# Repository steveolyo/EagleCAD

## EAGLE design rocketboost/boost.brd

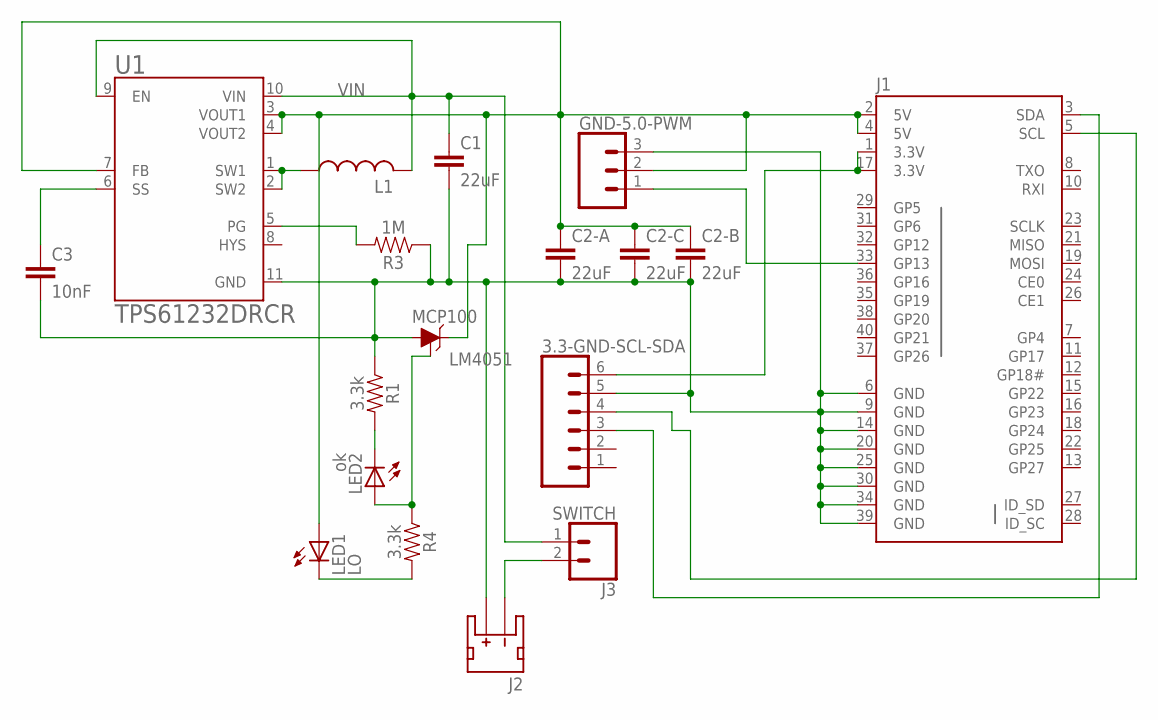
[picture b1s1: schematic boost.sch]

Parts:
3.3-GND-SCL-SDA: CONN_06POLAR; MOLEX-1X6
C1, C2-A, C2-B, C2-C: 22uF; C0603
C3: 10nF; C0603
GND-5.0-PWM: CONN_03; 1X03
J1: RASPBERRYPI-40-PIN-GPIO_PTH_NO_SHROUD; 2X20
J2: PWR; JST-2-SMD
J3: SWITCH; 1X02
L1: L-USL4532C; L4532M
LED1: LO; CHIP-LED0603
LED2: ok; CHIP-LED0603
MCP100: LM4051; SOT23-3
R1, R4: 3.3k; 0603
R3: 1M; 0603
U1: TPS61232DRCR; SON50P300X300X100-10N

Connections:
GND: 3.3-GND-SCL-SDA.5, C1.2, C2-A.2, C2-B.2, C2-C.2, C3.2, GND-5.0-PWM.3, J1.6 (GND), J1.9 (GND), J1.14 (GND), J1.20 (GND), J1.25 (GND), J1.30 (GND), J1.34 (GND), J1.39 (GND), J2.2 (+), MCP100.3 (A), R1.1, R3.1, U1.11 (GND)
unnamed: LED2.C, R1.2
unnamed: LED2.A, MCP100.1 (ADJ), R4.1
unnamed: GND-5.0-PWM.1, J1.33 (GP13)
unnamed: LED1.C, R4.2
unnamed: J2.1 (-), J3.2
PG: R3.2, U1.5 (PG)
SCL: 3.3-GND-SCL-SDA.4, J1.5 (SCL)
SDA: 3.3-GND-SCL-SDA.3, J1.3 (SDA)
SS: C3.1, U1.6 (SS)
SW: L1.1, U1.1 (SW1), U1.2 (SW2)
V33: 3.3-GND-SCL-SDA.6, J1.1 (3.3V), J1.17 (3.3V)
VIN: C1.1, J3.1, L1.2, U1.9 (EN), U1.10 (VIN)
VOUT: C2-A.1, C2-B.1, C2-C.1, GND-5.0-PWM.2, J1.2 (5V), J1.4 (5V), LED1.A, MCP100.2 (C), U1.3 (VOUT1), U1.4 (VOUT2), U1.7 (FB)

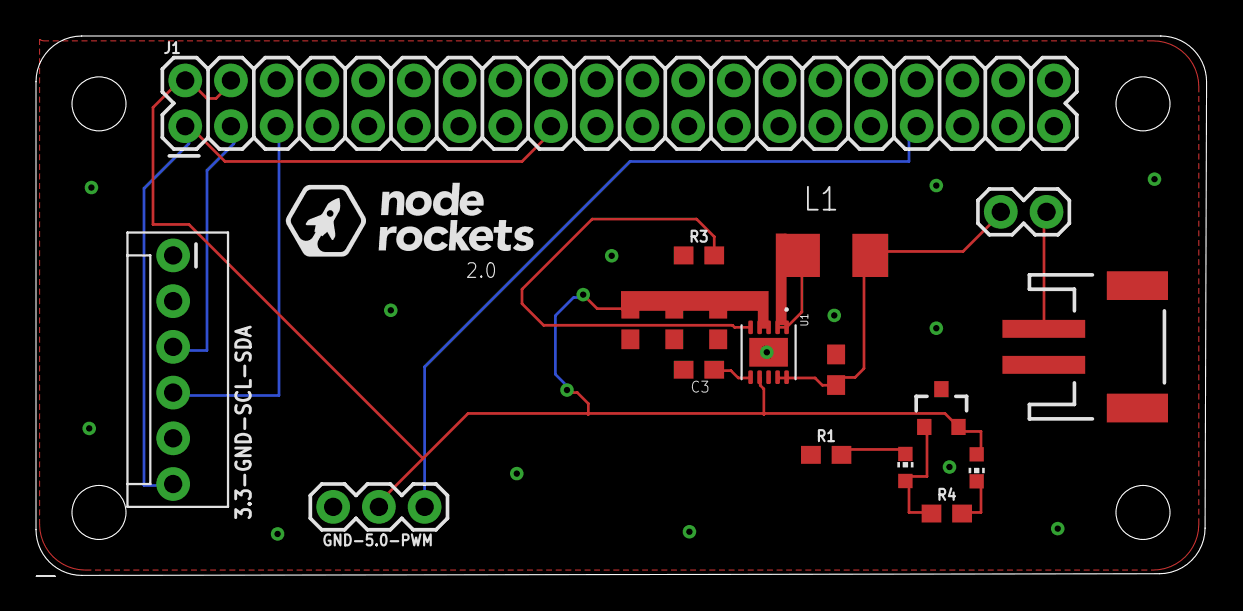
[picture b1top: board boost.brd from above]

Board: 2 copper layers, 65.0 x 30.0 mm, 18 parts (0 on the bottom side), 14 nets.

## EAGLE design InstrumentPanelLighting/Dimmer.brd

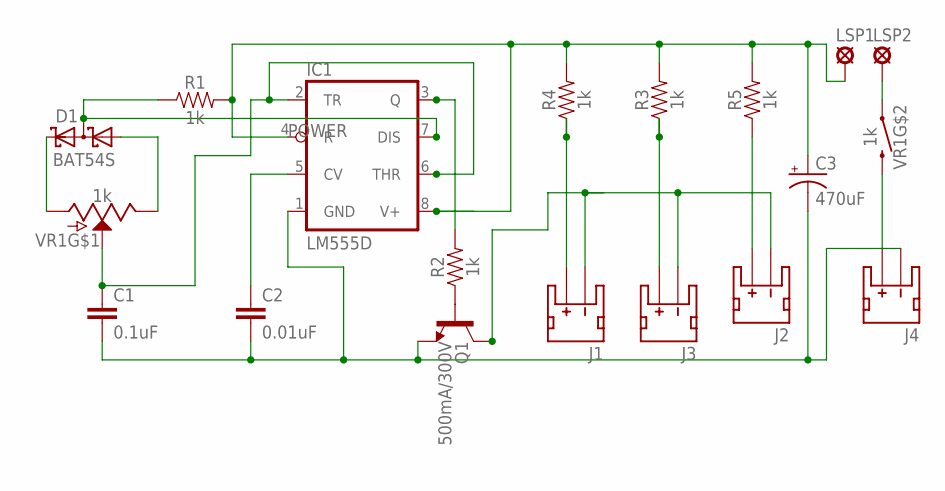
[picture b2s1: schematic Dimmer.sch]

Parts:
C1: 0.1uF; C0805
C2: 0.01uF; C0402
C3: 470uF; 085CS_1AW
D1: BAT54S; SOT23
IC1: LM555D; SO08
J1, J2, J3, J4: JST_2MM_MALE; JST-2-SMD
LSP1, LSP2: LSP10
Q1: 500mA/300V; SOT23-3
R1, R2, R3, R4, R5: 1k; 0603
VR1: 1k; POT-SWITCH-PTH

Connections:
B$2: C3.+, IC1.4 (R), IC1.8 (V+), LSP1.MP, R1.2, R3.2, R4.2, R5.2
GND: C1.2, C2.2, C3.-, IC1.1 (GND), J4.1 (-), Q1.2 (E)
unnamed: D1.1 (A1), VR1.3 (E)
unnamed: D1.2 (C2), VR1.1 (A)
unnamed: D1.3 (C1A2), IC1.7 (DIS), R1.1
unnamed: C2.1, IC1.5 (CV)
unnamed: C1.1, IC1.2 (TR), IC1.6 (THR), VR1.2 (S)
unnamed: Q1.1 (B), R2.1
unnamed: IC1.3 (Q), R2.2
unnamed: J1.1 (-), J2.1 (-), J3.1 (-), Q1.3 (C)
unnamed: J3.2 (+), R3.1
unnamed: LSP2.MP, VR1.S1 (1)
unnamed: J1.2 (+), R4.1
unnamed: J2.2 (+), R5.1
unnamed: J4.2 (+), VR1.S2 (2)

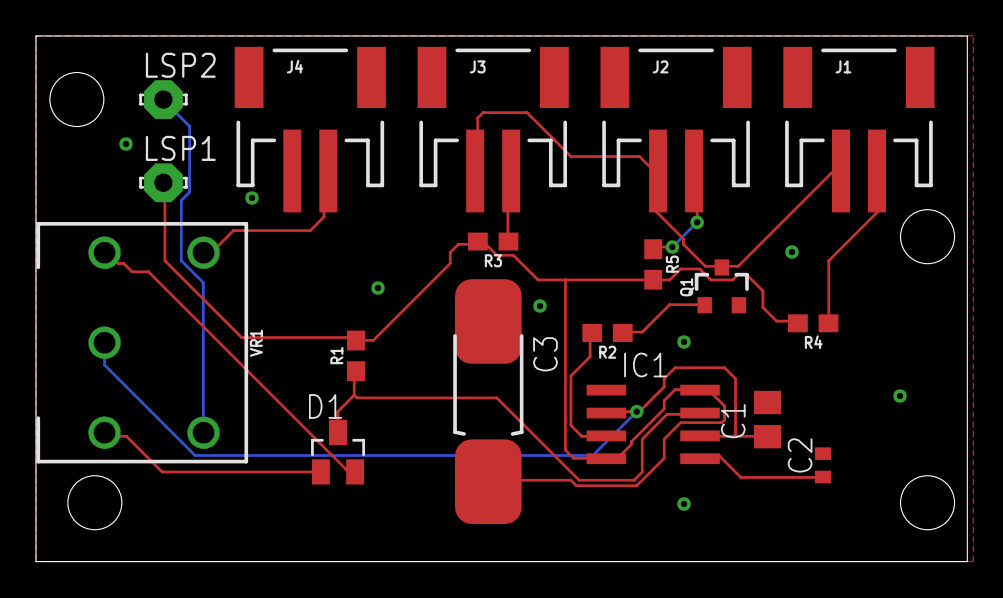
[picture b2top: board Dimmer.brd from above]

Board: 2 copper layers, 51.7 x 29.2 mm, 18 parts (0 on the bottom side), 15 nets.

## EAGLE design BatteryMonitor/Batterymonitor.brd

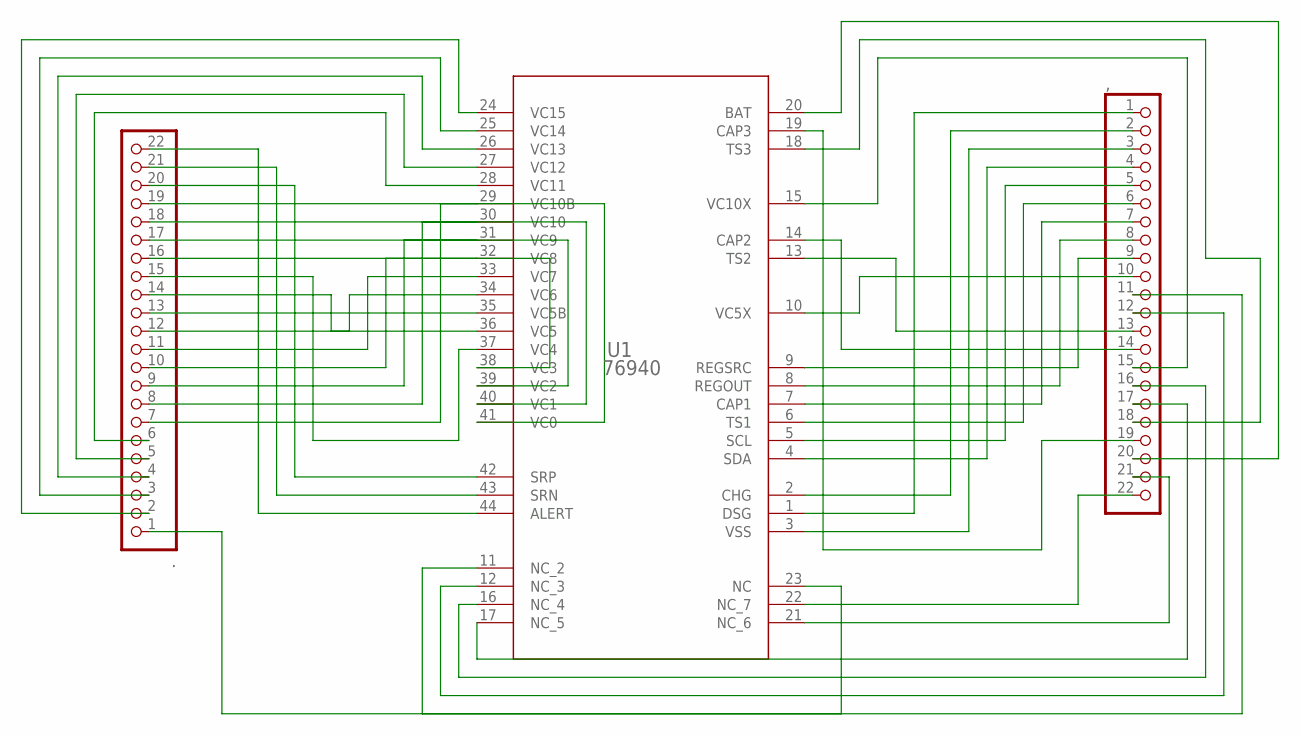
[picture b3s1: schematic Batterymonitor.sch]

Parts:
,: PINHD-1X22; 1X22
.: PINHD-1X22; 1X22
U1: 76940; DBT0044A_L

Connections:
unnamed: ..14, ..19, U1.36 (VC5), U1.41 (VC0)
unnamed: ,.1, U1.1 (DSG)
unnamed: ,.2, U1.2 (CHG)
unnamed: ,.3, U1.3 (VSS)
unnamed: ,.4, U1.4 (SDA)
unnamed: ,.5, U1.5 (SCL)
unnamed: ,.6, U1.6 (TS1)
unnamed: ,.7, U1.7 (CAP1)
unnamed: ,.8, U1.8 (REGOUT)
unnamed: ,.9, U1.9 (REGSRC)
unnamed: ,.10, U1.10 (VC5X)
unnamed: ,.11, U1.11 (NC_2)
unnamed: ,.12, U1.12 (NC_3)
unnamed: ,.13, U1.13 (TS2)
unnamed: ,.14, U1.14 (CAP2)
unnamed: ,.15, U1.15 (VC10X)
unnamed: ,.16, U1.16 (NC_4)
unnamed: ,.17, U1.17 (NC_5)
unnamed: ,.18, U1.18 (TS3)
unnamed: ,.19, U1.19 (CAP3)
unnamed: ,.20, U1.20 (BAT)
unnamed: ,.21, U1.21 (NC_6)
unnamed: ,.22, U1.22 (NC_7)
unnamed: ..1, U1.23 (NC)
unnamed: ..2, U1.24 (VC15)
unnamed: ..3, U1.25 (VC14)
unnamed: ..4, U1.26 (VC13)
unnamed: ..5, U1.27 (VC12)
unnamed: ..6, U1.28 (VC11)
unnamed: ..7, U1.29 (VC10B)
unnamed: ..8, U1.30 (VC10)
unnamed: ..9, U1.31 (VC9)
unnamed: ..10, U1.32 (VC8)
unnamed: ..11, U1.33 (VC7)
unnamed: ..12, U1.34 (VC6)
unnamed: ..13, U1.35 (VC5B)
unnamed: ..15, U1.37 (VC4)
unnamed: ..16, U1.38 (VC3)
unnamed: ..17, U1.39 (VC2)
unnamed: ..18, U1.40 (VC1)
unnamed: ..21, U1.43 (SRN)
unnamed: ..20, U1.42 (SRP)
unnamed: ..22, U1.44 (ALERT)

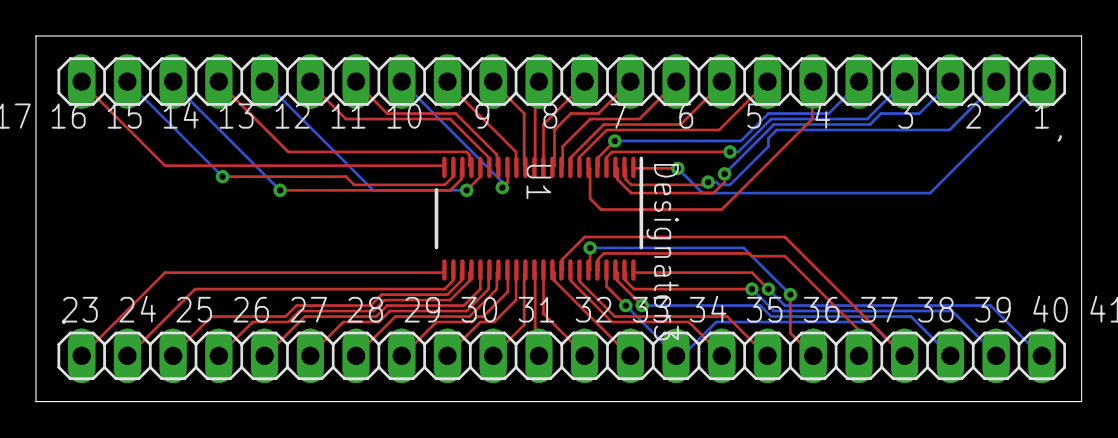
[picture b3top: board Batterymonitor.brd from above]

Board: 2 copper layers, 58.1 x 20.3 mm, 3 parts (0 on the bottom side), 43 nets.

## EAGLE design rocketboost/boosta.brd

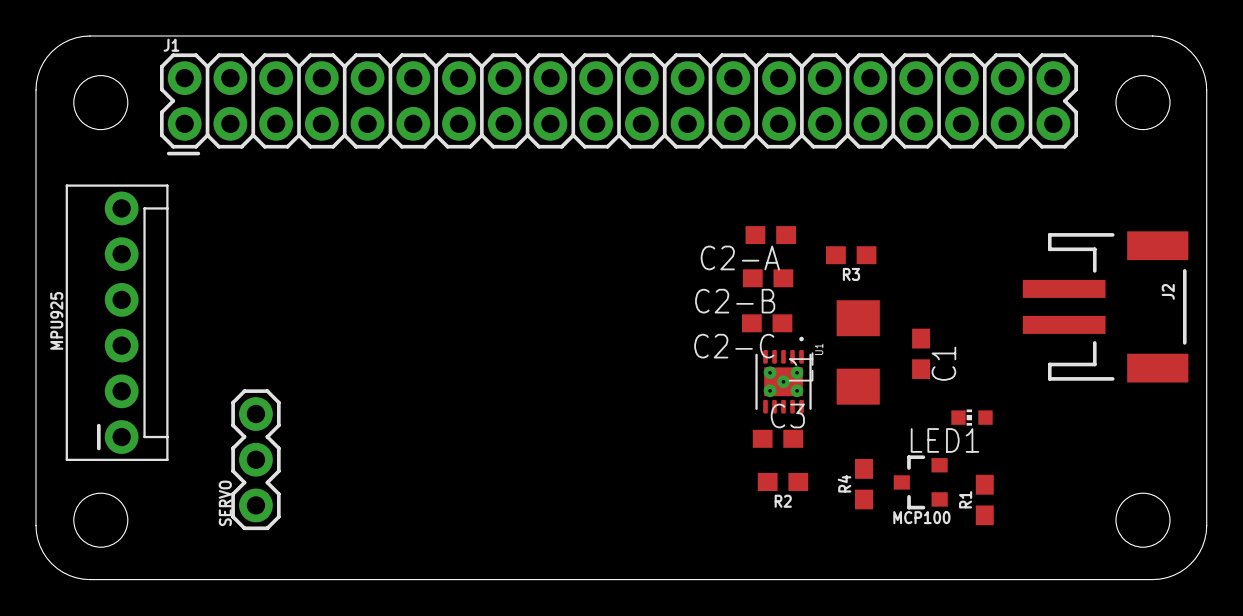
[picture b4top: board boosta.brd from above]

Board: 2 copper layers, 65.0 x 30.2 mm, 17 parts (0 on the bottom side), 14 nets, no tracks yet.

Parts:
C1, C2-A, C2-B, C2-C: 22uF; C0603
C3: 10nF; C0603
J1: 2X20
J2: JST-2-SMD
L1: L4532M
LED1: CHIP-LED0603
MCP100: LM4051; SOT23-3
MPU925: MOLEX-1X6
R1: 402K; 0603
R2: 100K; 0603
R3: 1M; 0603
R4: 3.3k; 0603
SERVO: 1X03
U1: TPS61232DRCR; SON50P300X300X100-10N

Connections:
unnamed: L1.1, U1.1
unnamed: C1.1, J2.2, L1.2, MCP100.2, U1.9, U1.10
unnamed: R3.2, U1.5
unnamed: MCP100.1, R4.1
unnamed: C2-A.1, C2-B.1, C2-C.1, J1.2, J1.4, LED1.A, R1.2, SERVO.2, U1.3
unnamed: C3.1, U1.6
unnamed: R1.1, R2.2, U1.7
unnamed: J1.6, SERVO.3
unnamed: J1.33, SERVO.1
unnamed: J1.1, J1.17, MPU925.6
unnamed: J1.5, MPU925.4
unnamed: J1.3, MPU925.3
unnamed: LED1.C, R4.2
unnamed: C1.2, C2-A.2, C2-B.2, C2-C.2, C3.2, J1.9, J1.14, J1.20, J1.25, J1.30, J1.34, J1.39, J2.1, MCP100.3, MPU925.5, R2.1, R3.1, U1.11

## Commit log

2019-05-01 commit readme
2019-05-01 rocketboost add
2019-05-01 adding svg logo
2019-06-19 board with ground proper to 61232
2019-06-19 adding logo
2019-07-03 ver 2.0

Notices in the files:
parts and their libraries:
SparkFun-Connectors: Licensing: Creative Commons ShareAlike 4.0 International - https://creativecommons.org/licenses/by-sa/4.0
